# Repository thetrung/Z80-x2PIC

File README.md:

# Z80 Homebrew with Dual 8-bit PIC 
Another PCB made for Z80 + 2x PIC18F4520 to debug, test-run & verify code.

### Note
I have never had a real working Z80 before so this board is designed to test that if I can get one.

### 3D Preview 

### Placement (SilkScreen)

### Schematic

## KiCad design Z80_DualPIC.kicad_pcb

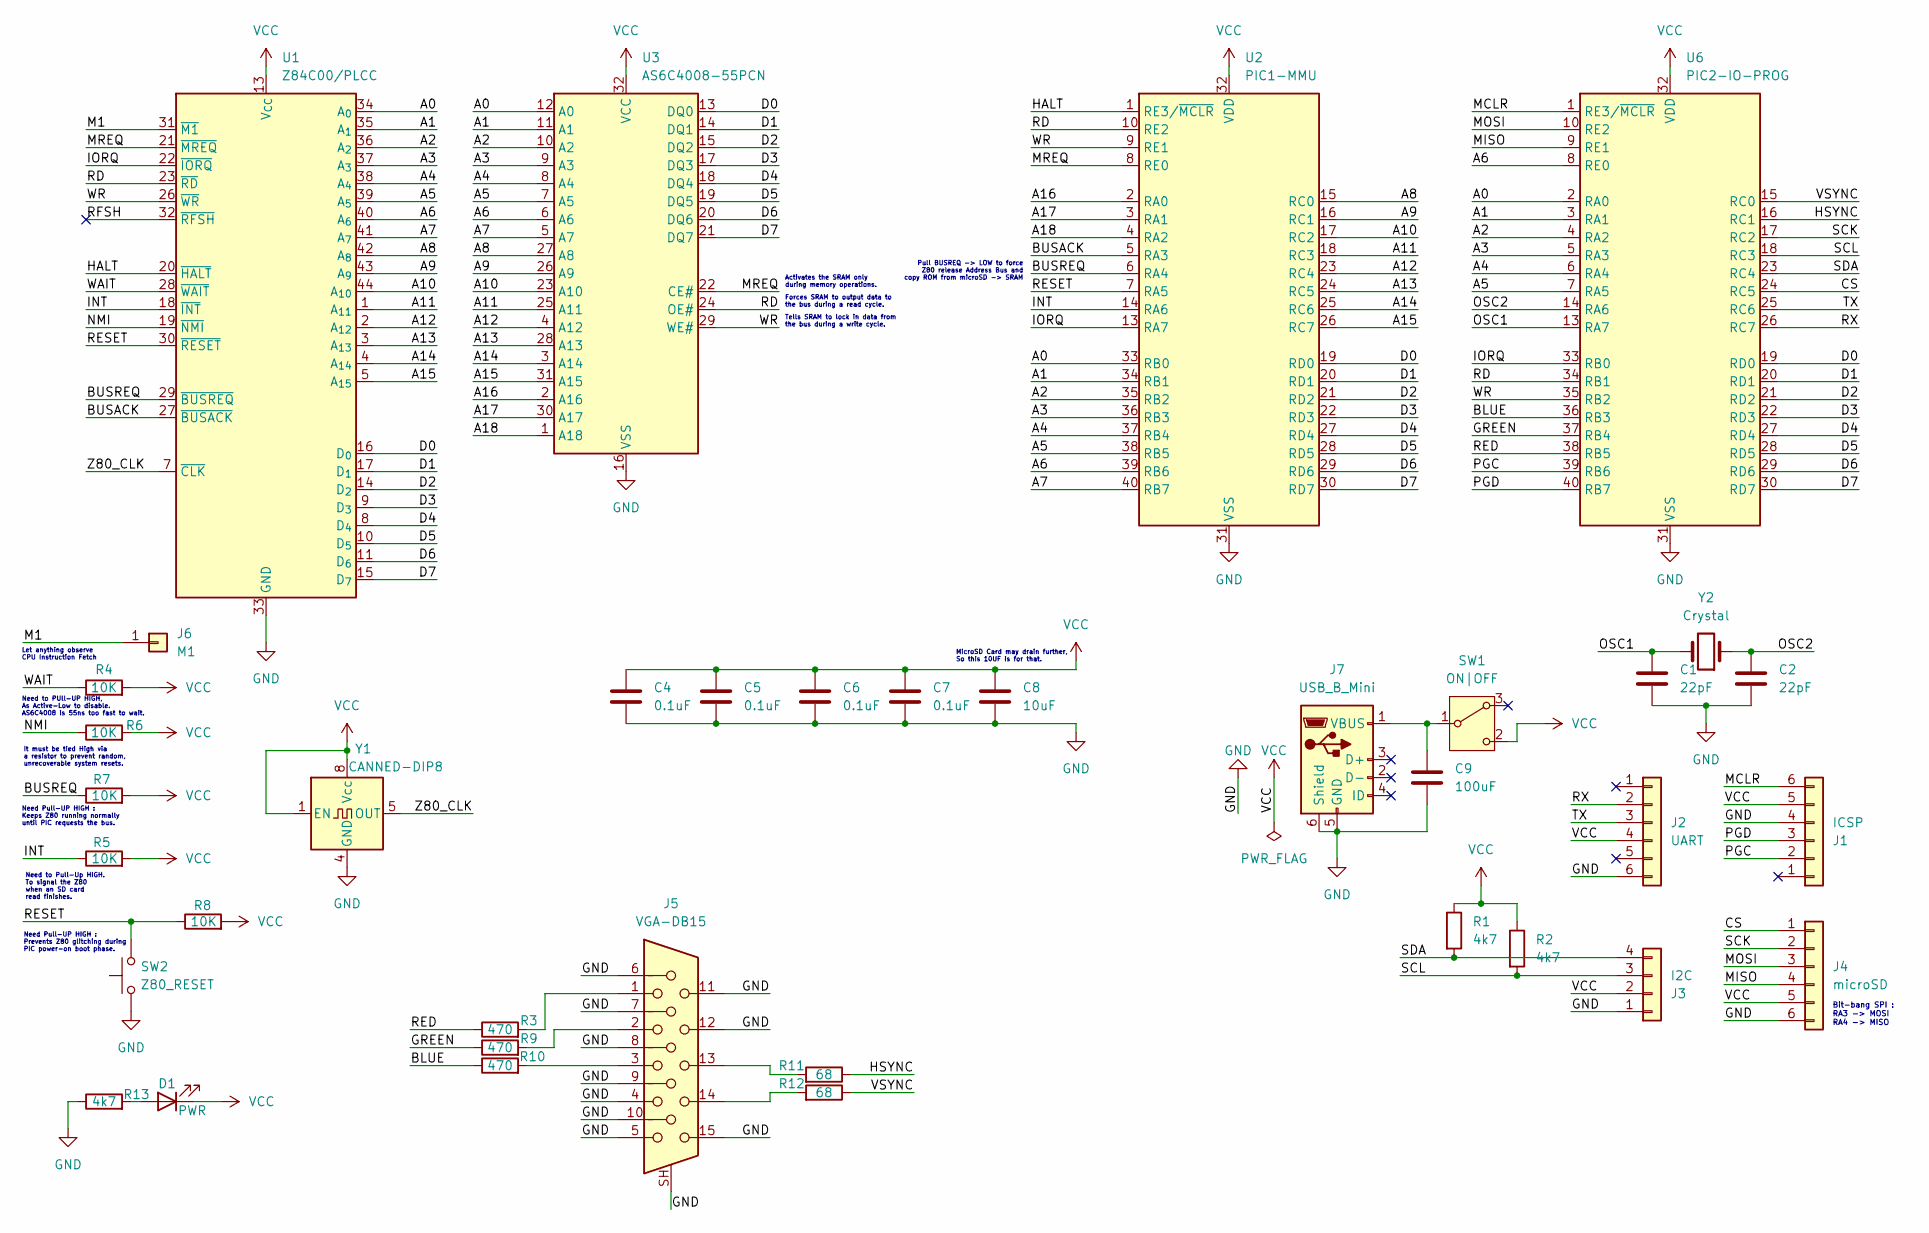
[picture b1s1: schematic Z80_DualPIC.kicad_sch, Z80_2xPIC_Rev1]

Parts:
C1, C2: 22pF; C_Disc_D3.4mm_W2.1mm_P2.50mm
C4, C5, C6, C7: 0.1uF; C_Disc_D3.4mm_W2.1mm_P2.50mm
C8: 10uF; C_Disc_D3.4mm_W2.1mm_P2.50mm
C9: 100uF; C_Radial_D4.0mm_H5.0mm_P1.50mm
D1: PWR; LED_D3.0mm
J1: ICSP; PinHeader_1x06_P2.54mm_Horizontal
J2: UART; PinHeader_1x06_P2.54mm_Vertical
J3: I2C; PinHeader_1x04_P2.54mm_Vertical
J4: microSD; PinSocket_1x06_P2.54mm_Vertical
J5: VGA-DB15; DSUB-15-HD_Socket_Horizontal_P2.29x2.54mm_EdgePinOffset8.35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
J6: M1; PinHeader_1x01_P2.54mm_Vertical
J7: USB_B_Mini; USB_MINI_B_90_Angled
R1, R2, R13: 4k7; R_Axial_DIN0207_L6.3mm_D2.5mm_P10.16mm_Horizontal
R3, R9, R10: 470; R_Axial_DIN0207_L6.3mm_D2.5mm_P10.16mm_Horizontal
R4, R5, R6, R7, R8: 10K; R_Axial_DIN0207_L6.3mm_D2.5mm_P10.16mm_Horizontal
R11, R12: 68; R_Axial_DIN0207_L6.3mm_D2.5mm_P10.16mm_Horizontal
SW1: ON|OFF; SW_Slide-03_Wuerth-WS-SLTV_10x2.5x6.4_P2.54mm
SW2: Z80_RESET; SW_PUSH_6mm
U1: Z84C00/PLCC; PLCC-44_THT-Socket
U2: PIC1-MMU; DIP-40_W15.24mm
U3: AS6C4008-55PCN; DIP-32_W15.24mm
U6: PIC2-IO-PROG; DIP-40_W15.24mm
Y1: CANNED-DIP8; Oscillator_DIP-8
Y2: Crystal; Crystal_HC49-4H_Vertical

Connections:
/A0: U1.34 (A_{0}), U2.33 (RB0), U3.12 (A0), U6.2 (RA0)
/A1: U1.35 (A_{1}), U2.34 (RB1), U3.11 (A1), U6.3 (RA1)
/A2: U1.36 (A_{2}), U2.35 (RB2), U3.10 (A2), U6.4 (RA2)
/A3: U1.37 (A_{3}), U2.36 (RB3), U3.9 (A3), U6.5 (RA3)
/A4: U1.38 (A_{4}), U2.37 (RB4), U3.8 (A4), U6.6 (RA4)
/A5: U1.39 (A_{5}), U2.38 (RB5), U3.7 (A5), U6.7 (RA5)
/A6: U1.40 (A_{6}), U2.39 (RB6), U3.6 (A6), U6.8 (RE0)
/A7: U1.41 (A_{7}), U2.40 (RB7), U3.5 (A7)
/A8: U1.42 (A_{8}), U2.15 (RC0), U3.27 (A8)
/A9: U1.43 (A_{9}), U2.16 (RC1), U3.26 (A9)
/A10: U1.44 (A_{10}), U2.17 (RC2), U3.23 (A10)
/A11: U1.1 (A_{11}), U2.18 (RC3), U3.25 (A11)
/A12: U1.2 (A_{12}), U2.23 (RC4), U3.4 (A12)
/A13: U1.3 (A_{13}), U2.24 (RC5), U3.28 (A13)
/A14: U1.4 (A_{14}), U2.25 (RC6), U3.3 (A14)
/A15: U1.5 (A_{15}), U2.26 (RC7), U3.31 (A15)
/A16: U2.2 (RA0), U3.2 (A16)
/A17: U2.3 (RA1), U3.30 (A17)
/A18: U2.4 (RA2), U3.1 (A18)
/BLUE: R10.1, U6.36 (RB3)
/BUSACK: U1.27 (~BUSACK), U2.5 (RA3)
/BUSREQ: R7.1, U1.29 (~BUSREQ), U2.6 (RA4)
/CS: J4.1, U6.24 (RC5)
/D0: U1.16 (D_{0}), U2.19 (RD0), U3.13 (DQ0), U6.19 (RD0)
/D1: U1.17 (D_{1}), U2.20 (RD1), U3.14 (DQ1), U6.20 (RD1)
/D2: U1.14 (D_{2}), U2.21 (RD2), U3.15 (DQ2), U6.21 (RD2)
/D3: U1.9 (D_{3}), U2.22 (RD3), U3.17 (DQ3), U6.22 (RD3)
/D4: U1.8 (D_{4}), U2.27 (RD4), U3.18 (DQ4), U6.27 (RD4)
/D5: U1.10 (D_{5}), U2.28 (RD5), U3.19 (DQ5), U6.28 (RD5)
/D6: U1.11 (D_{6}), U2.29 (RD6), U3.20 (DQ6), U6.29 (RD6)
/D7: U1.15 (D_{7}), U2.30 (RD7), U3.21 (DQ7), U6.30 (RD7)
/GREEN: R9.1, U6.37 (RB4)
/HALT: U1.20 (~HALT), U2.1 (RE3/~MCLR)
/HSYNC: R11.1, U6.16 (RC1)
/INT: R5.1, U1.18 (~INT), U2.14 (RA6)
/IORQ: U1.22 (~IORQ), U2.13 (RA7), U6.33 (RB0)
/M1: J6.1 (Pin_1_1), U1.31 (~M1)
/MCLR: J1.6, U6.1 (RE3/~MCLR)
/MISO: J4.4, U6.9 (RE1)
/MOSI: J4.3, U6.10 (RE2)
/MREQ: U1.21 (~MREQ), U2.8 (RE0), U3.22 (CE#)
/NMI: R6.1, U1.19 (~NMI)
/OSC1: C1.1, U6.13 (RA7), Y2.2
/OSC2: C2.1, U6.14 (RA6), Y2.1
/PGC: J1.2, U6.39 (RB6)
/PGD: J1.3, U6.40 (RB7)
/RD: U1.23 (~RD), U2.10 (RE2), U3.24 (OE#), U6.34 (RB1)
/RED: R3.1, U6.38 (RB5)
/RESET: R8.1, SW2.2, U1.30 (~RESET), U2.7 (RA5)
/RFSH: U1.32 (~RFSH)
/RX: J2.2, U6.26 (RC7)
/SCK: J4.2, U6.17 (RC2)
/SCL: J3.3, R2.2, U6.18 (RC3)
/SDA: J3.4, R1.2, U6.23 (RC4)
/TX: J2.3, U6.25 (RC6)
/VSYNC: R12.1, U6.15 (RC0)
/WAIT: R4.1, U1.28 (~WAIT)
/WR: U1.26 (~WR), U2.9 (RE1), U3.29 (WE#), U6.35 (RB2)
/Z80_CLK: U1.7 (~CLK), Y1.5 (OUT)
GND: C1.2, C2.2, C4.1, C5.1, C6.1, C7.1, C8.1, C9.1, J1.4, J2.6, J3.1, J4.6, J5.4, J5.5, J5.6, J5.7, J5.8, J5.9, J5.10, J5.11, J5.12, J5.15, J5.SH, J7.5 (GND), J7.6 (Shield), R13.1, SW2.1, U1.33 (GND), U2.12 (VSS), U2.31 (VSS), U3.16 (VSS), U6.12 (VSS), U6.31 (VSS), Y1.4 (GND)
unnamed: D1.2 (A), R13.2
unnamed: J5.1, R3.2
unnamed: J5.2, R9.2
unnamed: J5.3, R10.2
unnamed: J5.13, R11.2
unnamed: J5.14, R12.2
unnamed: C9.2, J7.1 (VBUS), SW1.1 (B)
VCC: C4.2, C5.2, C6.2, C7.2, C8.2, D1.1 (K), J1.5, J2.4, J3.2, J4.5, R1.1, R2.1, R4.2, R5.2, R6.2, R7.2, R8.2, SW1.2 (C), U1.13 (V_{CC}), U2.11 (VDD), U2.32 (VDD), U3.32 (VCC), U6.11 (VDD), U6.32 (VDD), Y1.1 (EN), Y1.8 (Vcc)

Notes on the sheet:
Activates the SRAM only during memory operations.
Bit-bang SPI : RA3 -> MOSI RA4 -> MISO
Need to Pull-Up HIGH. To signal the Z80 when an SD card read finishes.
Forces SRAM to output data to the bus during a read cycle.
It must be tied High via a resistor to prevent random, unrecoverable system resets.
MicroSD Card may drain further, So this 10UF is for that.
Need Pull-UP HIGH : Prevents Z80 glitching during PIC power-on boot phase.
Pull BUSREQ -> LOW to force Z80 release Address Bus and copy ROM from microSD -> SRAM
Need to PUll-UP HIGH, As Active-Low to disable. AS6C4008 is 55ns too fast to wait.
Need Pull-UP HIGH : Keeps Z80 running normally until PIC requests the bus.
Let anything observe CPU Instruction Fetch
Tells SRAM to lock in data from the bus during a write cycle.

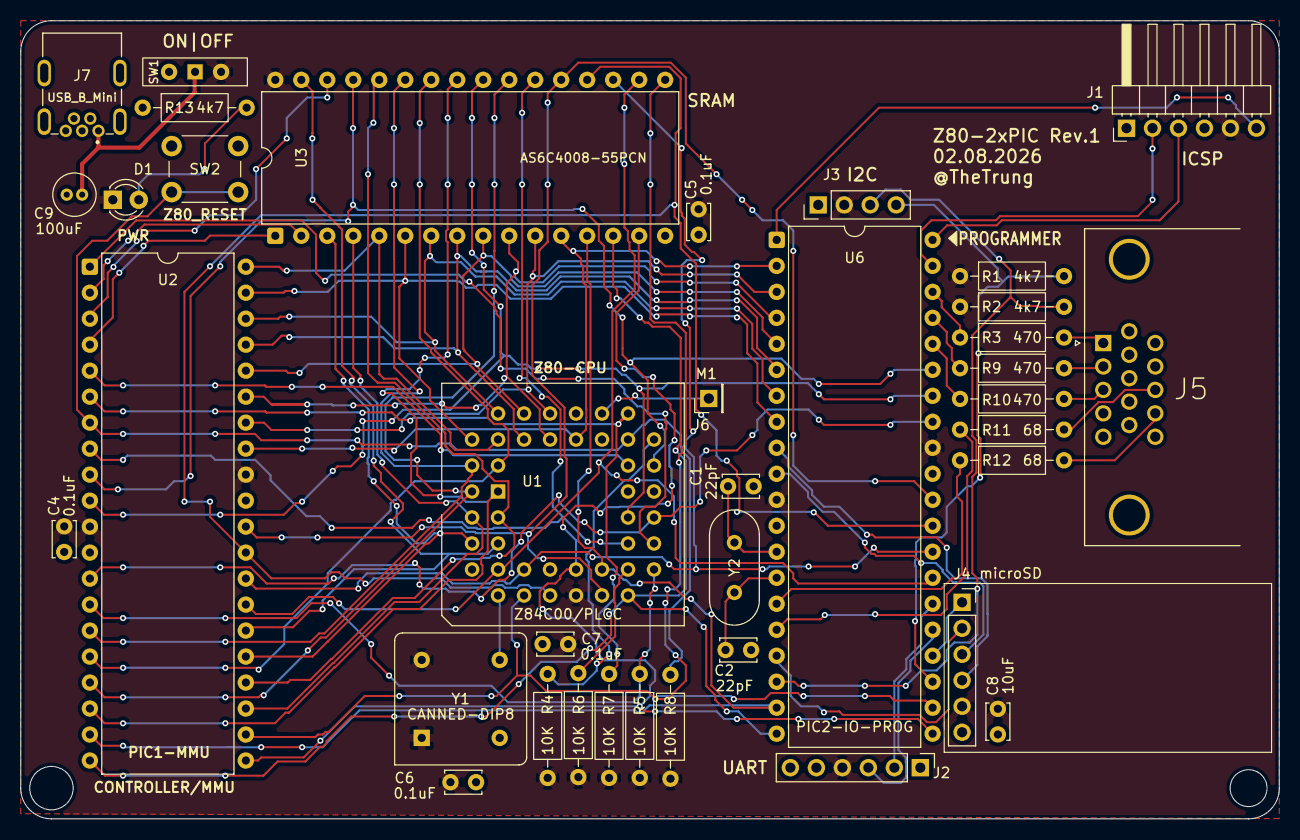
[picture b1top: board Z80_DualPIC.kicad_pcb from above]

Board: 2 copper layers, 123.0 x 78.0 mm, 37 parts (0 on the bottom side), 67 nets.
